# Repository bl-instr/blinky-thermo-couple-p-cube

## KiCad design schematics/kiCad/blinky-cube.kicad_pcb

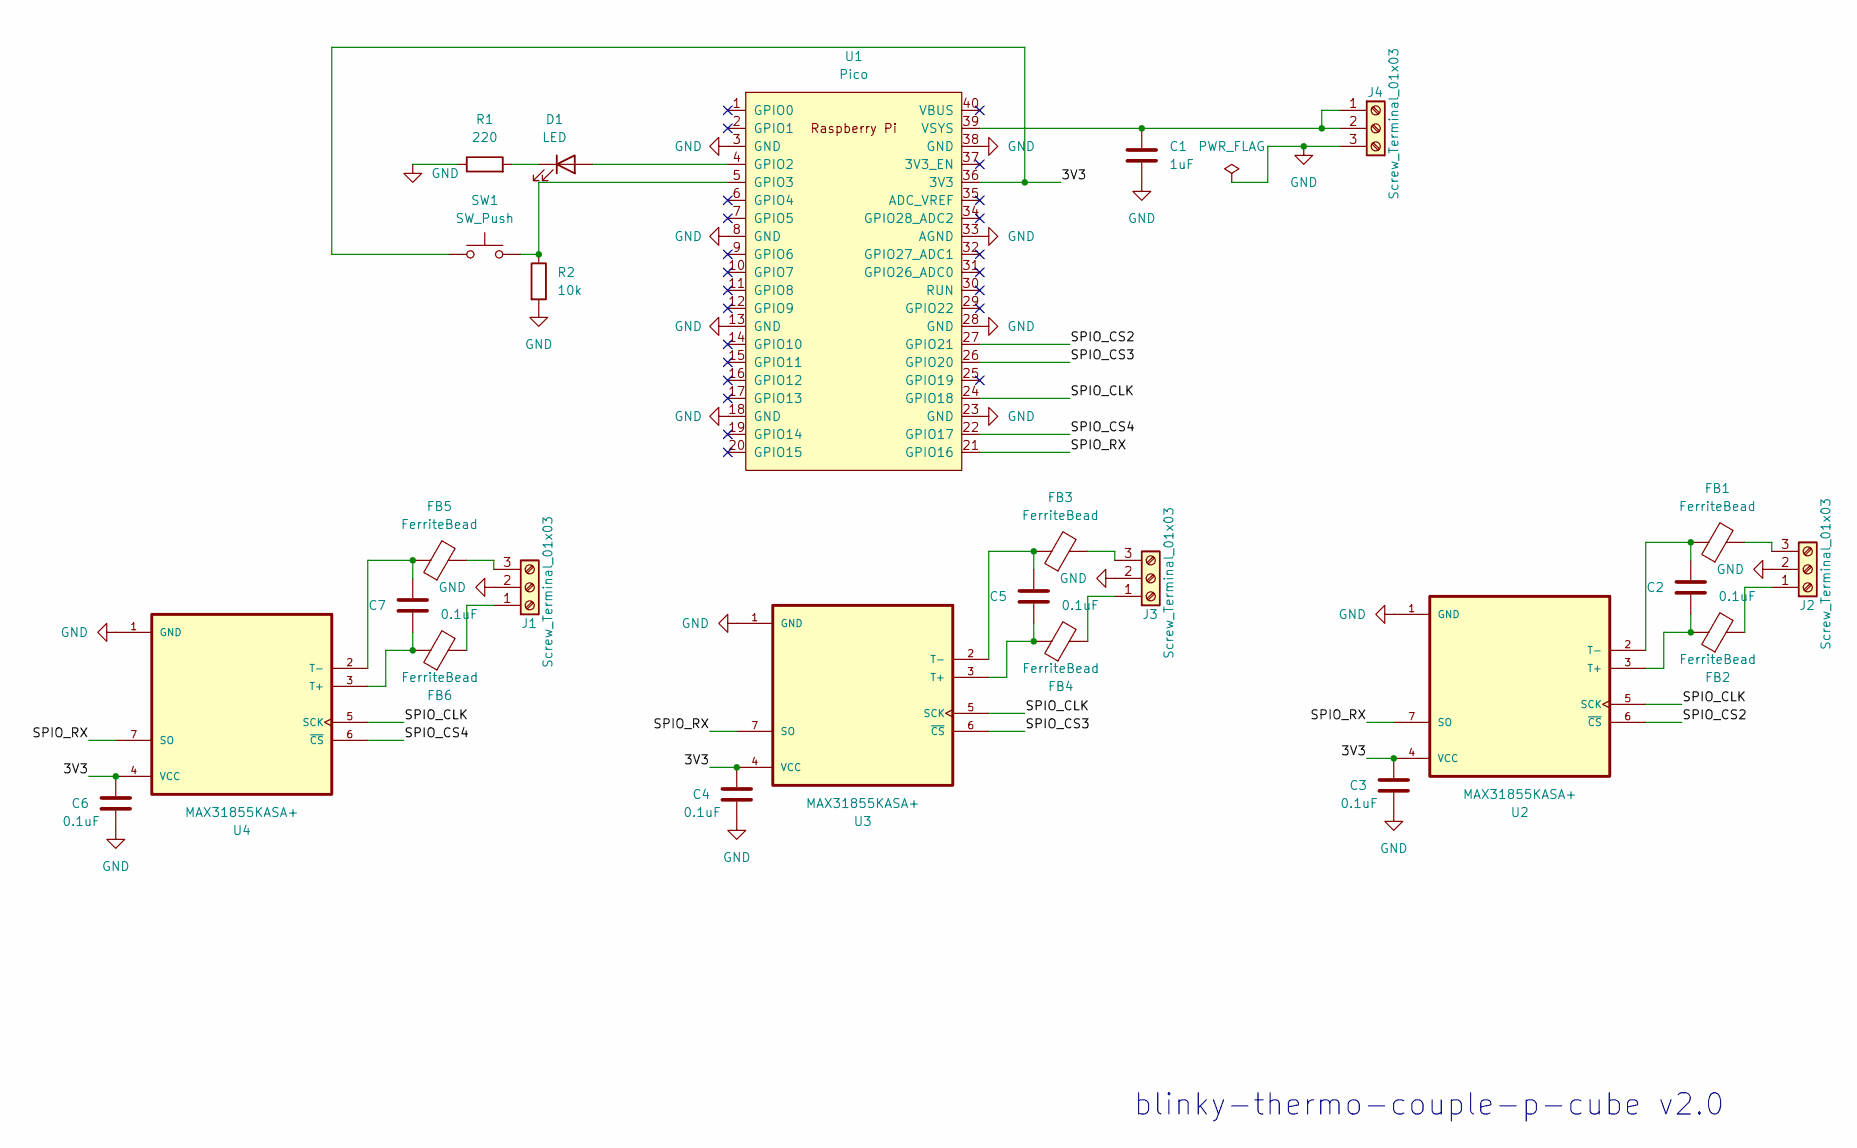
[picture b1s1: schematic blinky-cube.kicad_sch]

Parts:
C1: 1uF; C_1206_3216Metric_Pad1.33x1.80mm_HandSolder
C2, C3, C4, C5, C6, C7: 0.1uF; C_1206_3216Metric_Pad1.33x1.80mm_HandSolder
D1: LED; LED_D5.0mm
FB1, FB2, FB3, FB4, FB5, FB6: FerriteBead; L_1206_3216Metric_Pad1.42x1.75mm_HandSolder
J1, J2, J3, J4: Screw_Terminal_01x03; TerminalBlock_bornier-3_P5.08mm
R1: 220; R_1206_3216Metric_Pad1.30x1.75mm_HandSolder
R2: 10k; R_1206_3216Metric_Pad1.30x1.75mm_HandSolder
SW1: SW_Push; SW_PUSH_6mm
U1: Pico; RPi_Pico_SMD_TH
U2, U3, U4: MAX31855KASA+; SOIC127P600X175-8N

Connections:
/3V3: C3.1, C4.1, C6.1, SW1.1, U1.36 (3V3), U2.4 (VCC), U3.4 (VCC), U4.4 (VCC)
/SPIO_CLK: U1.24 (GPIO18), U2.5 (SCK), U3.5 (SCK), U4.5 (SCK)
/SPIO_CS2: U1.27 (GPIO21), U2.6 (~CS)
/SPIO_CS3: U1.26 (GPIO20), U3.6 (~CS)
/SPIO_CS4: U1.22 (GPIO17), U4.6 (~CS)
/SPIO_RX: U1.21 (GPIO16), U2.7 (SO), U3.7 (SO), U4.7 (SO)
GND: C1.2, C3.2, C4.2, C6.2, J1.2, J2.2, J3.2, J4.3, R1.1, R2.2, U1.3 (GND), U1.8 (GND), U1.13 (GND), U1.18 (GND), U1.23 (GND), U1.28 (GND), U1.33 (AGND), U1.38 (GND), U2.1 (GND), U3.1 (GND), U4.1 (GND)
unnamed: D1.2 (A), U1.4 (GPIO2)
unnamed: D1.1 (K), R1.2
unnamed: FB6.2, J1.1
unnamed: FB5.2, J1.3
unnamed: FB2.2, J2.1
unnamed: FB1.2, J2.3
unnamed: FB4.2, J3.1
unnamed: FB3.2, J3.3
unnamed: C1.1, J4.1, J4.2, U1.39 (VSYS)
unnamed: R2.1, SW1.2, U1.5 (GPIO3)
unnamed: C2.2, FB2.1, U2.3 (T+)
unnamed: C2.1, FB1.1, U2.2 (T-)
unnamed: C5.2, FB4.1, U3.3 (T+)
unnamed: C5.1, FB3.1, U3.2 (T-)
unnamed: C7.2, FB6.1, U4.3 (T+)
unnamed: C7.1, FB5.1, U4.2 (T-)

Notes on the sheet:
blinky-thermo-couple-p-cube v2.0

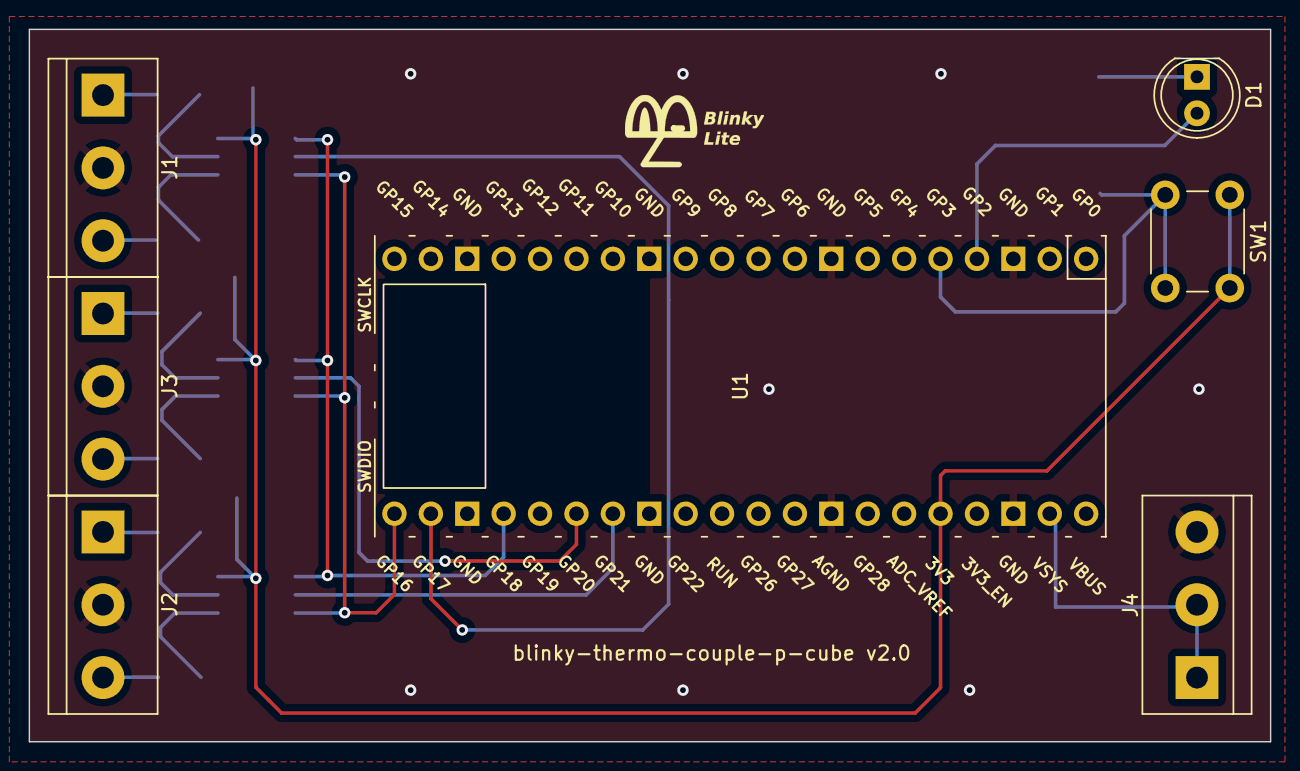
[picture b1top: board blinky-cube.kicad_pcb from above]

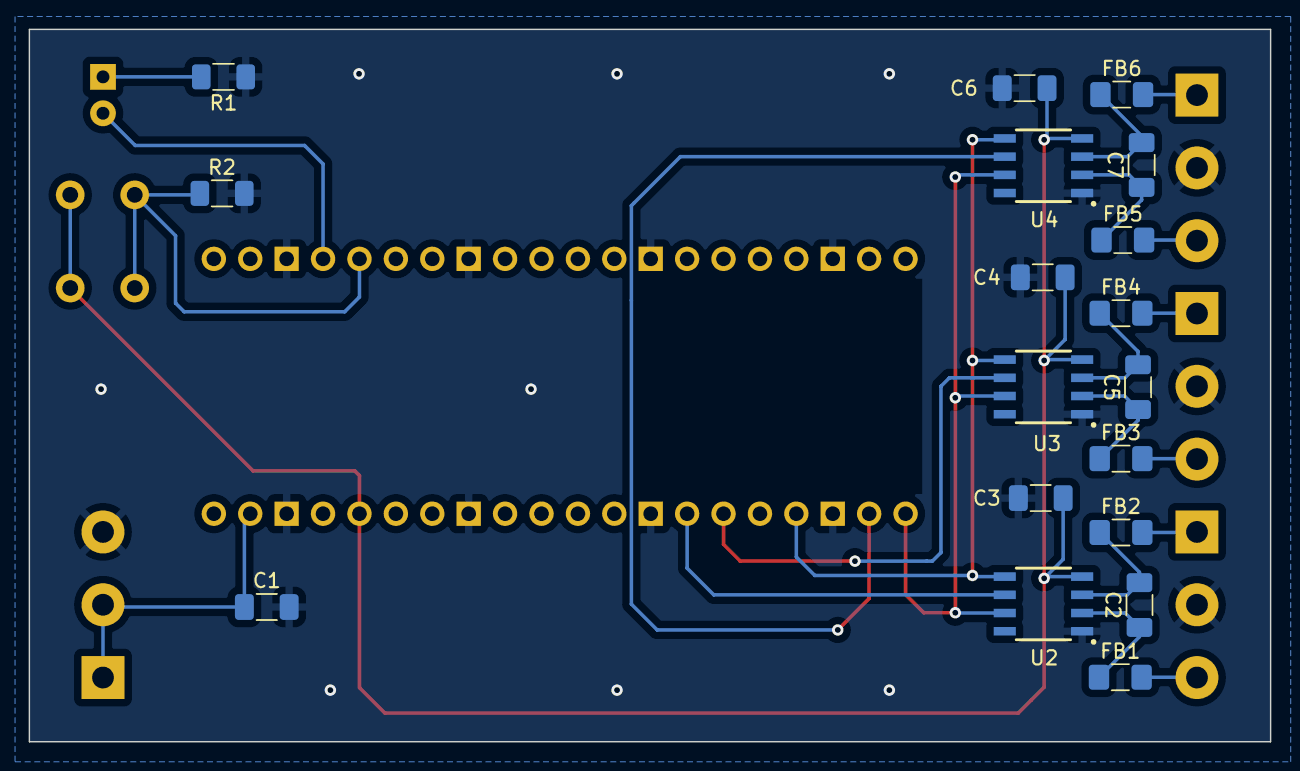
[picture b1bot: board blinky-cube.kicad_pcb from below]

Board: 2 copper layers, 86.6 x 49.7 mm, 25 parts (18 on the bottom side), 23 nets.

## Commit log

2022-11-06 wifi cred change working
2022-11-08 web working
2022-11-10 fixed mqtt timeout
2022-11-12 latest with class strucutre
2022-11-12 new class structure
2022-11-15 added hardware watch dog and reboot on wireless change
2022-11-17 working with DS18B20 also fixed mem problem on pico
2022-11-17 updated cred examples
2023-01-28 added new schematic
2023-01-29 working with new circuit card
2023-12-08 updated to b5
2023-12-08 added print diag
2024-01-20 schematic in DIN mode 3 format
2024-01-20 added schem pics
2024-02-22 added bom
2024-03-03 added wifi reboot after too may attempts
2024-03-09 reading max31855
2024-03-16 cleanup
2024-03-20 added one-core
2024-05-07 added 10ms delays on spi trans to remove glitches
2025-02-13 working with picoW
